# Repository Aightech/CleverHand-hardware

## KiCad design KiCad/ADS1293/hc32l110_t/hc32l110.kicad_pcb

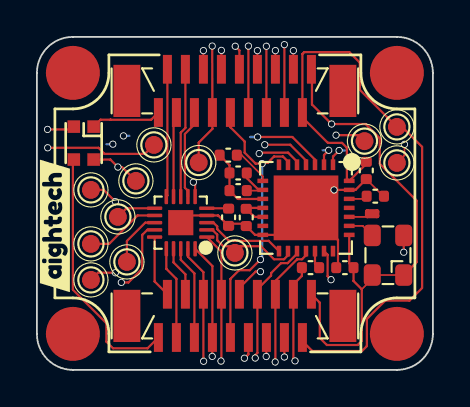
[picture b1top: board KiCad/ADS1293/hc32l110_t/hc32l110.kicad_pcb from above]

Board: 4 copper layers, 22.0 x 18.5 mm, 32 parts (0 on the bottom side), 34 nets.

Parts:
C3, C5, C7: 100nF; C_0402_1005Metric
C4: 1nF; C_0402_1005Metric
C6: 1uF; C_0402_1005Metric
C8: 4.7uF; C_0402_1005Metric
I1, I2, I3, I4: smd_insert; insert_1.2mm
J1, J2: XF2J-1824-12A
LED1: WS2812-2020
R1: 10K; C_0402_1005Metric
R2: 10M; C_0402_1005Metric
R3: 51; C_0402_1005Metric
TP1, TP2, TP3, TP4, TP9, TP10: TP_SDA; TestPoint_Pad_D1.0mm
TP5: TP_SCL; TestPoint_Pad_D1.0mm
TP6: TP_AUX1; TestPoint_Pad_D1.0mm
TP7, TP11, TP12: TP_AUX2; TestPoint_Pad_D1.0mm
TP8: TP_AUX3; TestPoint_Pad_D1.0mm
U1: ADS1293CISQE-NOPB; ADS1293CISQE
U2: HC32L110C6UA; QFN-20-1EP_3x3mm_P0.4mm_EP1.4x1.4mm
XTAL1: 4.096MHz; SMD3225-4P
kibuzzard-63F61033: G***; kibuzzard-63F61033

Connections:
+3.3V: C7.1, J1.18, J2.1, LED1.4 (VDD), TP12.1, U1.22 (VDDIO), U2.6 (AVCC), XTAL1.1 (EN), XTAL1.4 (VDD)
+5VA: C5.1, J1.17, J2.2, TP11.1, U1.28 (VDD)
/ADS1293CISQE_0402_unit/CMOUT: R1.2, U1.8 (CMOUT)
/ADS1293CISQE_0402_unit/RLDINV: C4.1, R1.1, R2.1, U1.10 (RLDINV)
/ADS1293CISQE_0402_unit/RLDOUT: C4.2, R2.2, U1.9 (RLDOUT)
/ADS1293CISQE_0402_unit/RLDREF: C3.1, U1.11 (RLDIN), U1.12 (RLDREF)
/ADS1293CISQE_0402_unit/XTAL2: U1.23 (XTAL1), XTAL1.3 (o)
/ADS1293CISQE_0402_unit/cvref: C6.1, U1.26 (CVREF)
/ADS1293CISQE_0402_unit/sdo: R3.1, U1.19 (SDO)
/Vcap: C8.2, U2.5 (Vcap)
ADD_IN1: J1.2, U2.15 (GPIO)
ADD_IN2: J1.3, U2.16 (GPIO)
ADD_IN3: J1.4, U2.17 (GPIO)
ADD_IN4: J1.5, U2.18 (GPIO)
ADD_OUT1: J2.17, U2.10 (GPIO)
ADD_OUT2: J2.16, U2.9 (GPIO)
ADD_OUT3: J2.15, U2.8 (GPIO)
ADD_OUT4: J2.14, U2.7 (GPIO)
AUX1: J1.11, J2.8, TP6.1
AUX2: J1.13, J2.6, TP8.1
CSB: TP1.1, U1.16 (CSB), U2.2 (GPIO)
DIN: J1.14, J2.5, U1.18 (SDI)
DOUT: J1.16, J2.3, R3.2
GND: C3.2, C5.2, C6.2, C7.2, C8.1, J1.10, J1.15, J2.4, J2.9, LED1.2 (GND), TP10.1, U1.14 (VSSIO), U1.27 (VSS), U1.29 (EPAD), U2.4 (GND), U2.21 (GPIO), XTAL1.2 (GND)
I2C_SCL: J1.7, J2.12, TP5.1, U2.20 (I2C_SCL)
I2C_SDA: J1.6, J2.13, TP4.1, U2.19 (I2C_SDA)
IN_ref: J1.9, J2.10, U1.6 (IN6)
LED_IN: J1.1, LED1.3 (DI)
LED_OUT: J2.18, LED1.1 (DO)
OUT1: TP2.1, U2.13 (GPIO)
OUT2: TP3.1, U2.12 (GPIO)
OUT3: TP9.1, U2.11 (GPIO)
RESETB: J1.8, J2.11, TP7.1, U2.1 (RESETB)
SCLK: J1.12, J2.7, U1.17 (SCLK)

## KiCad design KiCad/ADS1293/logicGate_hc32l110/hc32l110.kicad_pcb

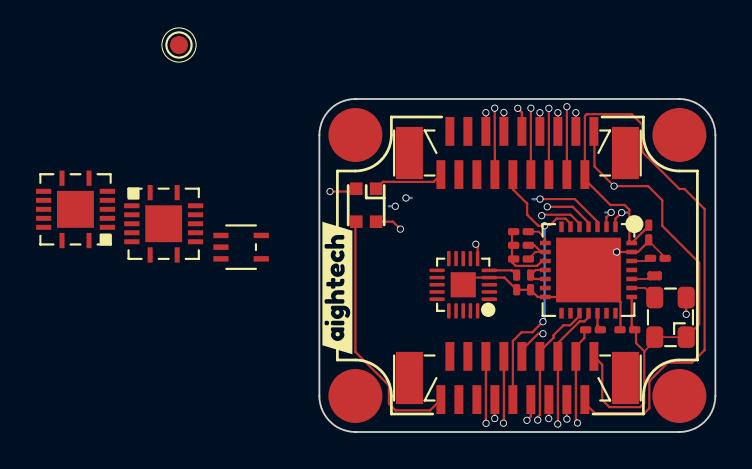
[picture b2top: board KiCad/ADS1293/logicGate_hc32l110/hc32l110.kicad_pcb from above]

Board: 8 copper layers, 22.0 x 18.5 mm, 24 parts (0 on the bottom side), 34 nets.

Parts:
C3, C5, C7: 100nF; C_0201_0603Metric_Pad0.64x0.40mm_HandSolder
C4: 1nF; C_0201_0603Metric_Pad0.64x0.40mm_HandSolder
C6: 1uF; C_0201_0603Metric_Pad0.64x0.40mm_HandSolder
C8: 4.7uF; C_0201_0603Metric_Pad0.64x0.40mm_HandSolder
I1, I2, I3, I4: smd_insert; insert_1.2mm
J1, J2: XF2J-1824-12A
LED1: WS2812-2020
R1: 10K; R_0201_0603Metric_Pad0.64x0.40mm_HandSolder
R2: 10M; R_0201_0603Metric_Pad0.64x0.40mm_HandSolder
R3: 51; R_0201_0603Metric_Pad0.64x0.40mm_HandSolder
TP1: TP_SDA; TestPoint_Pad_D1.0mm
U1: ADS1293CISQE-NOPB; ADS1293CISQE
U2: HC32L110C6UA; QFN-20-1EP_3x3mm_P0.4mm_EP1.4x1.4mm
U3: SN74ALVC08RGYR
U4: SN74LVC86ARGYR
U5: SN74LVC1G132DCKR
XTAL1: 4.096MHz; SMD3225-4P
kibuzzard-63F61033: G***; kibuzzard-63F61033

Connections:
+3.3V: C7.1, J1.18, J2.1, LED1.4 (VDD), U1.22 (VDDIO), U2.6 (AVCC), U3.1 (1A), U3.14 (VCC), U4.5 (2B), U4.14 (VCC), U5.5 (VCC), XTAL1.1 (EN), XTAL1.4 (VDD)
+5VA: C5.1, J1.17, J2.2, U1.28 (VDD)
/ADS1293CISQE_0402_unit/CMOUT: R1.2, U1.8 (CMOUT)
/ADS1293CISQE_0402_unit/RLDINV: C4.1, R1.1, R2.1, U1.10 (RLDINV)
/ADS1293CISQE_0402_unit/RLDOUT: C4.2, R2.2, U1.9 (RLDOUT)
/ADS1293CISQE_0402_unit/RLDREF: C3.1, U1.11 (RLDIN), U1.12 (RLDREF)
/ADS1293CISQE_0402_unit/XTAL2: U1.23 (XTAL1), XTAL1.3 (o)
/ADS1293CISQE_0402_unit/cvref: C6.1, U1.26 (CVREF)
/ADS1293CISQE_0402_unit/sdo: R3.1, U1.19 (SDO)
/Vcap: C8.2, U2.5 (Vcap)
/addressing/carry0: U3.3 (1Y), U3.4 (2A), U4.2 (1B)
/addressing/carry1: U3.6 (2Y), U3.9 (3A), U4.13 (4B)
/addressing/carry2: U3.8 (3Y), U4.10 (3B), U5.1 (A)
ADD_IN1: J1.2, U3.2 (1B), U4.4 (2A)
ADD_IN2: J1.3, U3.5 (2B), U4.1 (1A)
ADD_IN3: J1.4, U3.10 (3B), U4.12 (4A)
ADD_IN4: J1.5, U4.9 (3A), U5.2 (B)
ADD_OUT1: J2.17, U4.6 (2Y)
ADD_OUT2: J2.16, U4.3 (1Y)
ADD_OUT3: J2.15, U4.11 (4Y)
ADD_OUT4: J2.14, U4.8 (3Y)
AUX1: J1.11, J2.8, U2.15 (SWCLK)
AUX2: J1.13, J2.6, U2.14 (SWDIO)
CSB: TP1.1, U1.16 (CSB), U2.2 (GPIO), U5.4 (Y)
DIN: J1.14, J2.5, U1.18 (SDI)
DOUT: J1.16, J2.3, R3.2
GND: C3.2, C5.2, C6.2, C7.2, C8.1, J1.10, J1.15, J2.4, J2.9, LED1.2 (GND), U1.14 (VSSIO), U1.27 (VSS), U1.29 (EPAD), U2.4 (GND), U2.21 (GPIO), U3.7 (GND), U3.15 (EPAD), U4.7 (GND), U4.15 (EPAD), U5.3 (GND), XTAL1.2 (GND)
I2C_SCL: J1.7, J2.12, U2.20 (I2C_SCL)
I2C_SDA: J1.6, J2.13, U2.19 (I2C_SDA)
IN_ref: J1.9, J2.10, U1.6 (IN6)
LED_IN: J1.1, LED1.3 (DI), U2.18 (GPIO)
LED_OUT: J2.18, LED1.1 (DO)
RESETB: J1.8, J2.11, U2.1 (RESETB)
SCLK: J1.12, J2.7, U1.17 (SCLK)

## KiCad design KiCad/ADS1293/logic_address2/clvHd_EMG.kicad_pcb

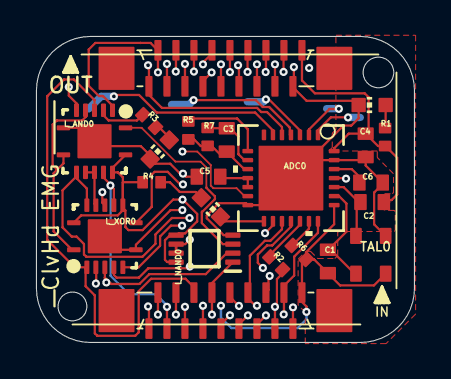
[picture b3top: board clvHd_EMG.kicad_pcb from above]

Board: 4 copper layers, 21.0 x 17.0 mm, 25 parts (0 on the bottom side), 37 nets.

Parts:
@HOLE0, @HOLE1: (no value)
ADC0: ADS1293CISQ/NOPB; RSG28_3P6X3P6_TEX
C1, C2: 22pF; C0402
C3: 1nF; C0402
C4, C5: 100nF; C0402
C6: 1uF; C0402
L1: Green; CHIP-LED0603
L2: Red; CHIP-LED0603
L3: White; CHIP-LED0603
L_AND0: SN74ALVC08; VQFN-14-CUSTOM
L_NAND0: SN74AUP2G00; VSSOP
L_XOR0: SN74LVC86; VQFN-14-CUSTOM
R1, R2, R3, R4: 51; R0402
R5: 10k; R0402
R6: 1M; R0402
R7: 10M; R0402
TAL0: C387328; SMD-3225_4P
UNK1, UNK2: X05C2018TZ

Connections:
A0: L_AND0.12, L_XOR0.10, UNK1.3
A1: L_AND0.9, L_XOR0.13, UNK1.5
A2: L_AND0.4, L_XOR0.2, UNK1.6
A3: L_NAND0.1, L_XOR0.5, UNK1.8
ALARMB: ADC0.15, L2.C
CLK: ADC0.21, UNK1.16, UNK2.3
CMOUT: ADC0.8, R5.1
CS: ADC0.16, L_NAND0.6, L_NAND0.7
DIN: ADC0.18, UNK1.13, UNK2.6
DOUT: R2.2, UNK1.15, UNK2.4
DRDYB: ADC0.20, R6.1
GND: ADC0.14, ADC0.27, ADC0.29, C4.2, C5.2, C6.2, L1.C, L3.C, L_AND0.7, L_AND0.15, L_NAND0.4, L_XOR0.7, L_XOR0.15, TAL0.2, UNK1.4, UNK1.7, UNK1.11, UNK1.14, UNK1.17, UNK2.2, UNK2.5, UNK2.8, UNK2.12, UNK2.15
GPIO1: L_AND0.2, UNK1.2, UNK2.17
IN5: ADC0.5, UNK1.1, UNK2.18
unnamed: L_AND0.1, L_NAND0.3
unnamed: L1.A, R1.2
unnamed: ADC0.19, R2.1
unnamed: ADC0.23, C1.2, TAL0.4
unnamed: L_AND0.3, R3.2
unnamed: L2.A, R4.1
unnamed: L3.A, R3.1
unnamed: ADC0.24, C2.2, TAL0.3
unnamed: ADC0.26, C6.1
unnamed: L_AND0.10, L_AND0.11, L_XOR0.12
unnamed: L_AND0.5, L_AND0.8, L_XOR0.1
unnamed: ADC0.10, C3.1, R5.2, R7.2
unnamed: L_AND0.6, L_NAND0.2, L_XOR0.4
RLDOUT: ADC0.9, C3.2, R7.1
RLDREF: ADC0.11, ADC0.12, C5.1
RST: ADC0.25, UNK1.9, UNK2.10
S0: L_XOR0.8, UNK2.16
S1: L_XOR0.11, UNK2.14
S2: L_XOR0.3, UNK2.13
S3: L_XOR0.6, UNK2.11
SCLK: ADC0.17, UNK1.12, UNK2.7
SYNCB: ADC0.13, UNK1.10, UNK2.9
VDD: ADC0.22, ADC0.28, C1.1, C2.1, C4.1, L_AND0.13, L_AND0.14, L_NAND0.5, L_NAND0.8, L_XOR0.9, L_XOR0.14, R1.1, R4.2, R6.2, TAL0.1, UNK1.18, UNK2.1

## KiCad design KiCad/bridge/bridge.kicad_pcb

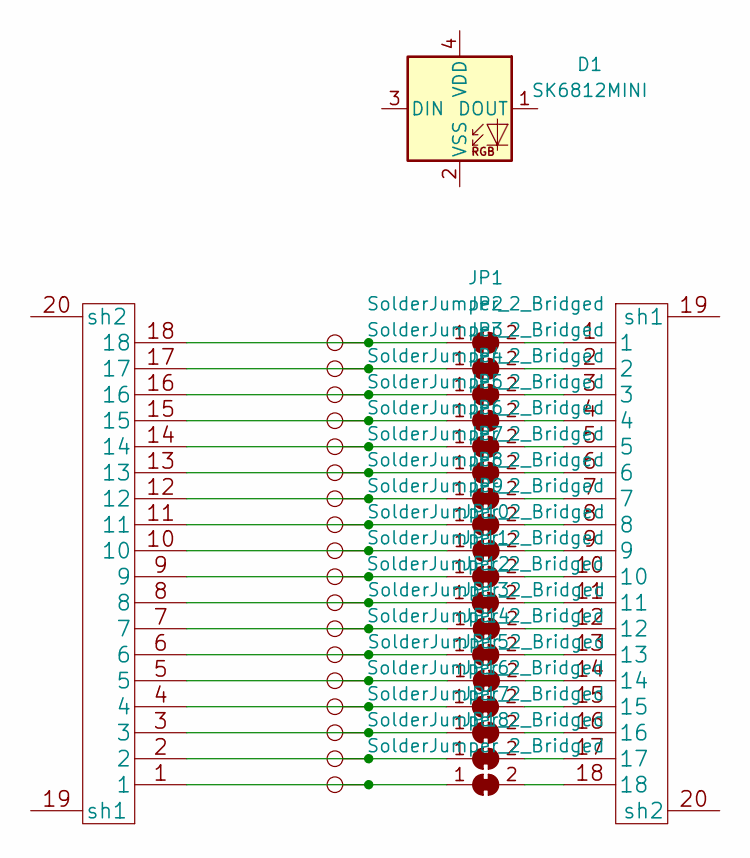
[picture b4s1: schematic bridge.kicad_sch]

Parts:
D1: SK6812MINI; LED_SK6812MINI_PLCC4_3.5x3.5mm_P1.75mm
J1, J2: XF2J-1824-12A
JP1, JP2, JP3, JP4, JP5, JP6, JP7, JP8, JP9, JP10, JP11, JP12, JP13, JP14, JP15, JP16, JP17, JP18: SolderJumper_2_Bridged; SolderJumper-2_P1.3mm_Bridged_RoundedPad1.0x1.5mm
TP1, TP2, TP3, TP4, TP5, TP6, TP7, TP8, TP9, TP10, TP11, TP12, TP13, TP14, TP15, TP16, TP17, TP18: TestPoint; TestPoint_Pad_D1.5mm

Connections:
unnamed: J1.1, JP18.1 (A), TP18.1
unnamed: J1.2, JP17.1 (A), TP17.1
unnamed: J1.3, JP16.1 (A), TP16.1
unnamed: J1.4, JP15.1 (A), TP15.1
unnamed: J1.5, JP14.1 (A), TP14.1
unnamed: J1.6, JP13.1 (A), TP13.1
unnamed: J1.7, JP12.1 (A), TP12.1
unnamed: J1.8, JP11.1 (A), TP11.1
unnamed: J1.9, JP10.1 (A), TP10.1
unnamed: J1.10, JP9.1 (A), TP9.1
unnamed: J1.11, JP8.1 (A), TP8.1
unnamed: J1.12, JP7.1 (A), TP7.1
unnamed: J1.13, JP6.1 (A), TP6.1
unnamed: J1.14, JP5.1 (A), TP5.1
unnamed: J1.15, JP4.1 (A), TP4.1
unnamed: J1.16, JP3.1 (A), TP3.1
unnamed: J1.17, JP2.1 (A), TP2.1
unnamed: J1.18, JP1.1 (A), TP1.1
unnamed: J2.1, JP1.2 (B)
unnamed: J2.2, JP2.2 (B)
unnamed: J2.3, JP3.2 (B)
unnamed: J2.4, JP4.2 (B)
unnamed: J2.5, JP5.2 (B)
unnamed: J2.6, JP6.2 (B)
unnamed: J2.7, JP7.2 (B)
unnamed: J2.8, JP8.2 (B)
unnamed: J2.9, JP9.2 (B)
unnamed: J2.10, JP10.2 (B)
unnamed: J2.11, JP11.2 (B)
unnamed: J2.12, JP12.2 (B)
unnamed: J2.13, JP13.2 (B)
unnamed: J2.14, JP14.2 (B)
unnamed: J2.15, JP15.2 (B)
unnamed: J2.16, JP16.2 (B)
unnamed: J2.17, JP17.2 (B)
unnamed: J2.18, JP18.2 (B)

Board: 2 copper layers, 39 parts (0 on the bottom side), 36 nets, no tracks yet.

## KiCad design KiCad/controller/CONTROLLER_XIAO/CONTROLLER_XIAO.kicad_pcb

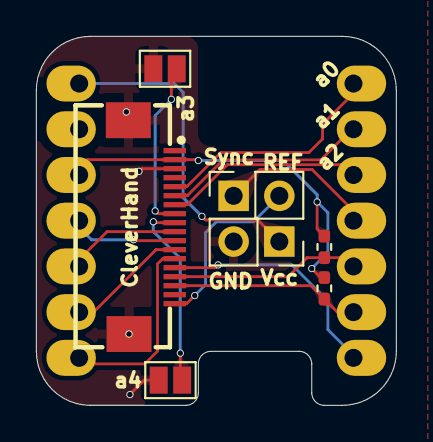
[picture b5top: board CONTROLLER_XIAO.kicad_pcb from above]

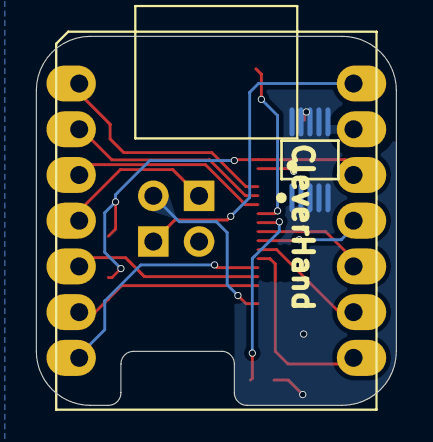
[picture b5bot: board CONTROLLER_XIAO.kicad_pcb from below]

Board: 4 copper layers, 20.0 x 20.5 mm, 9 parts (2 on the bottom side), 17 nets.

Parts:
FPC1: FPC-05F-18PH20; FPC-SMD_18P-P0.50_FPC-05F-18PH20
J1, J3: Conn_01x02_Pin; PinHeader_1x02_P2.54mm_Vertical
JP1, JP2: SolderJumper_2_Open; SolderJumper-2_P1.3mm_Open_Pad1.0x1.5mm
R1, R2: 2k; R_0402_1005Metric_Pad0.72x0.64mm_HandSolder
U1: MCP4728A0T-E/UNVAO; MSOP-10_L3.0-W3.0-P0.50-LS5.0-BL
U2: SEEEDUINO-XIAO-ESP32C3; xiaoSeeedStudio_MODULE14P-DIP

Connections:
+3.3V: FPC1.2, R1.1, R2.1, U2.12 (3V3)
/I2C_SDA: FPC1.15, R2.2, U2.5 (PA8_A4_D4_SDA)
/IO1_out: FPC1.13, U2.8 (PB09_A7_D7_RX)
/IO2: FPC1.14, U2.7 (PB08_A6_D6_TX)
/PICO: FPC1.11, U2.11 (PA6_A10_D10_MOSI)
/POCI: FPC1.10, U2.10 (PA5_A9_D9_MISO)
/SCLK: FPC1.12, U2.9 (PA7_A8_D8_SCK)
/Sync: J3.1, U2.4 (PA11_A3_D3)
/addr_bus_0: FPC1.5, U2.1 (PA02_A0_D0)
/addr_bus_1: FPC1.6, U2.2 (PA4_A1_D1)
/addr_bus_2: FPC1.7, U2.3 (PA10_A2_D2)
/addr_bus_3: FPC1.8, JP2.1 (A)
/addr_bus_4: FPC1.9, JP1.1 (A)
/extRef: FPC1.18, J1.2
/i2C_SCL: FPC1.16, R1.2, U2.6 (PA9_A5_D5_SCL)
GND: FPC1.3, FPC1.19, FPC1.20, J3.2, JP1.2 (B), JP2.2 (B), U2.13 (GND)
VSYS: J1.1, U2.14 (5V)

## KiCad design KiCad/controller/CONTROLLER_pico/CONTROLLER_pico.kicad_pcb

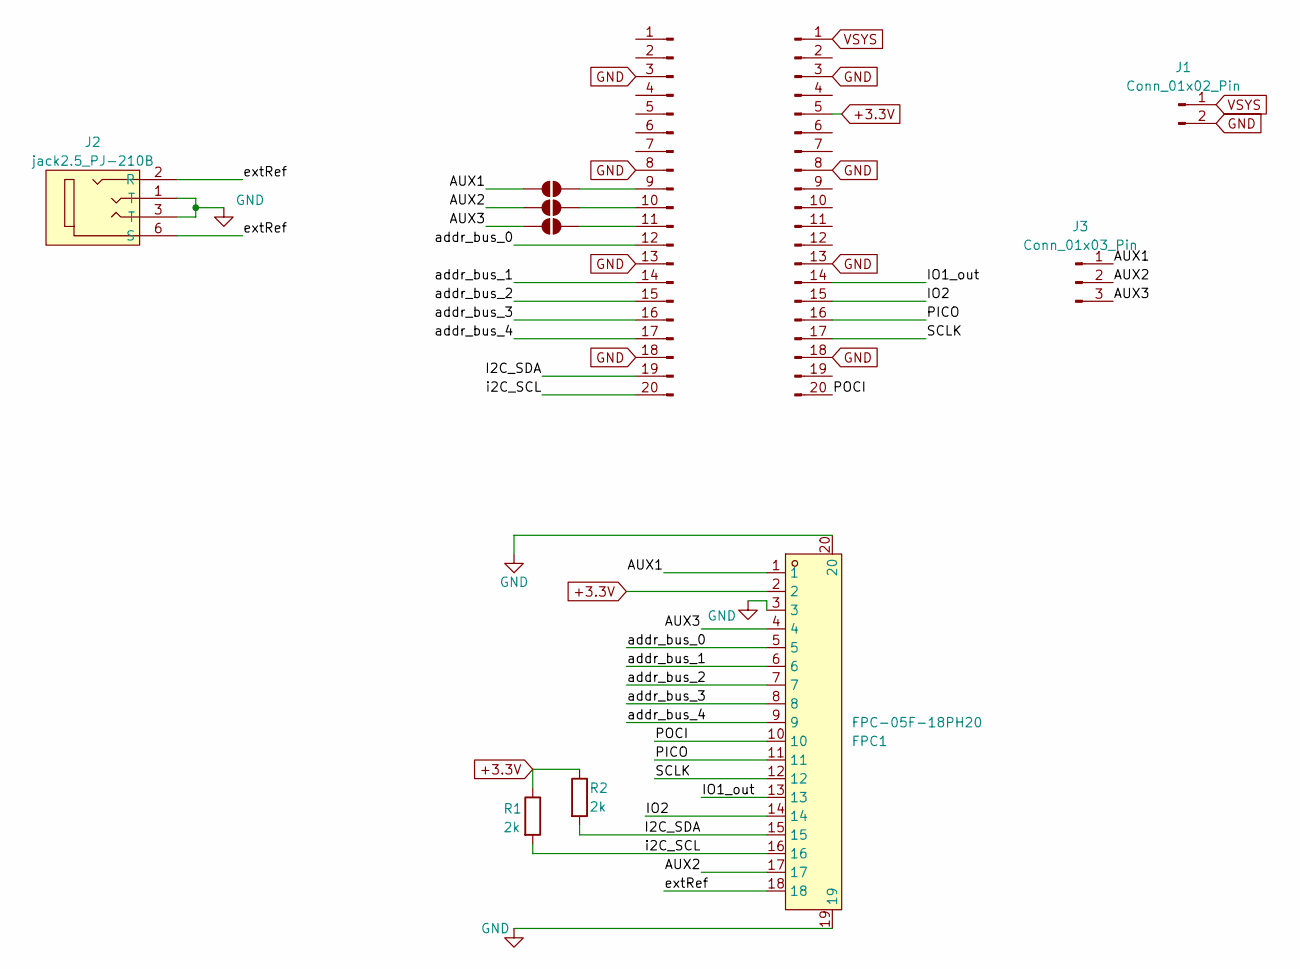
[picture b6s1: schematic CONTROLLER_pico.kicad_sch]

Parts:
FPC1: FPC-05F-18PH20; FPC-SMD_18P-P0.50_X05C2018TZ; LCSC Part C397324
J1: Conn_01x02_Pin; PinHeader_1x02_P1.27mm_Vertical
J2: jack2.5_PJ-210B; Jack_Socket_PJ-210B
J3: Conn_01x03_Pin; PinSocket_1x03_P1.27mm_Vertical
J4, J5: Conn_01x20_Male; PinHeader_1x20_P2.54mm_Vertical
JP2, JP3, JP4: SolderJumper_2_Open; SolderJumper-2_P1.3mm_Open_TrianglePad1.0x1.5mm
R1, R2: 2k; R_0402_1005Metric_Pad0.72x0.64mm_HandSolder; LCSC Part C4109

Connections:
+3.3V: FPC1.2, J5.5, R1.1, R2.1
/AUX1: FPC1.1, J3.1, JP2.1 (A)
/AUX2: FPC1.17, J3.2, JP3.1 (A)
/AUX3: FPC1.4, J3.3, JP4.1 (A)
/I2C_SDA: FPC1.15, J4.19, R2.2
/IO1_out: FPC1.13, J5.14
/IO2: FPC1.14, J5.15
/PICO: FPC1.11, J5.16
/POCI: FPC1.10, J5.20
/SCLK: FPC1.12, J5.17
/addr_bus_0: FPC1.5, J4.12
/addr_bus_1: FPC1.6, J4.14
/addr_bus_2: FPC1.7, J4.15
/addr_bus_3: FPC1.8, J4.16
/addr_bus_4: FPC1.9, J4.17
/extRef: FPC1.18, J2.2 (R), J2.6 (S)
/i2C_SCL: FPC1.16, J4.20, R1.2
GND: FPC1.3, FPC1.19, FPC1.20, J1.2, J2.1 (T), J2.3 (T), J4.3, J4.8, J4.13, J4.18, J5.3, J5.8, J5.13, J5.18
unnamed: J4.9, JP2.2 (B)
unnamed: J4.10, JP3.2 (B)
unnamed: J4.11, JP4.2 (B)
VSYS: J1.1, J5.1

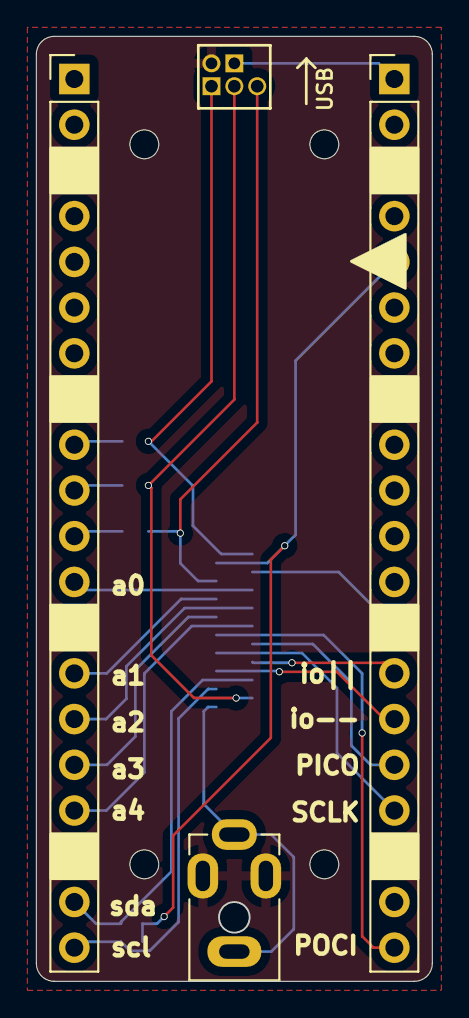
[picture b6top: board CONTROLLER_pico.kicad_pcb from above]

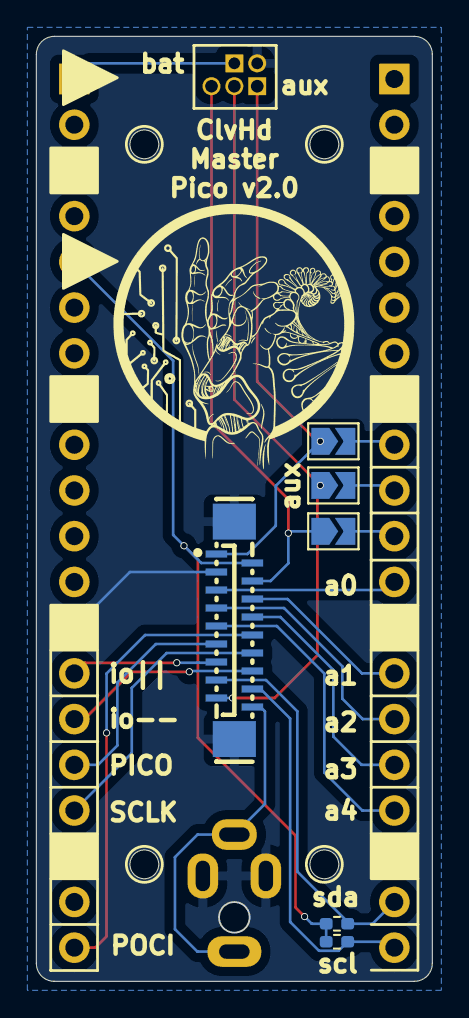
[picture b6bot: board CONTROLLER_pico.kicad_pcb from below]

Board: 4 copper layers, 22.0 x 52.5 mm, 11 parts (6 on the bottom side), 22 nets.
